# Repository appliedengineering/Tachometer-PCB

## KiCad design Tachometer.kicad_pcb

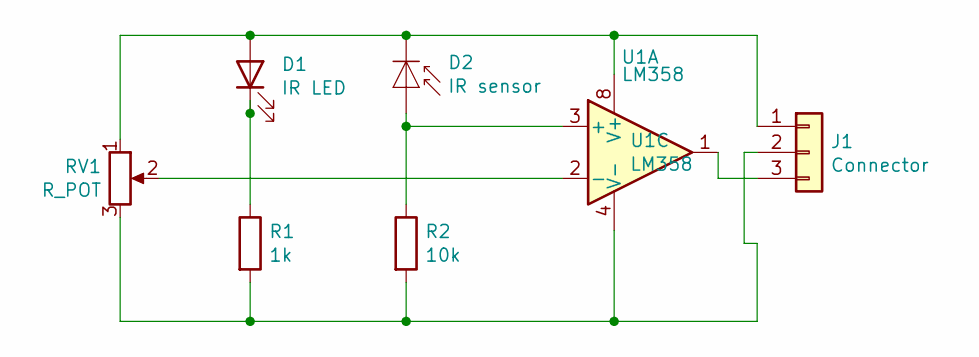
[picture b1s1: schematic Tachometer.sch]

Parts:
D1: IR LED; LED_D3.0mm_IRBlack
D2: IR sensor; LED_D3.0mm_IRBlack
J1: Connector; PinHeader_1x03_P2.54mm_Vertical
R1: 1k; R_Axial_DIN0207_L6.3mm_D2.5mm_P7.62mm_Horizontal
R2: 10k; R_Axial_DIN0207_L6.3mm_D2.5mm_P7.62mm_Horizontal
RV1: R_POT; Potentiometer_Bourns_3296W_Vertical
U1: LM358

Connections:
unnamed: D1.1 (K), R1.1
unnamed: D1.2 (A), D2.1 (K), J1.1, RV1.1, U1.8 (V+)
unnamed: D2.2 (A), R2.1, U1.3 (+)
unnamed: J1.2, R1.2, R2.2, RV1.3, U1.4 (V-)
unnamed: J1.3, U1.1
unnamed: RV1.2, U1.2 (-)

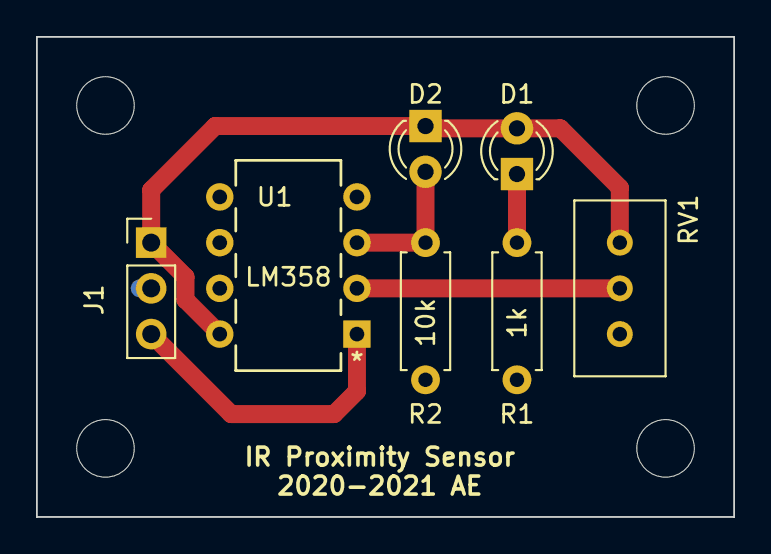
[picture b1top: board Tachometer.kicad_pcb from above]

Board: 2 copper layers, 38.7 x 26.7 mm, 11 parts (0 on the bottom side), 6 nets.

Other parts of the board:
MH1, MH2, MH3, MH4: MountingHole_3.2mm_M3

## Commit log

2020-12-07 new folder
2020-12-07 gerber files upload

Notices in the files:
parts and their libraries:
Copyright 2016 Accelerated Designs. All rights reserved.
